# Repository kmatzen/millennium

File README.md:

# Millennium Project

The **Millennium Project** breathes new life into the Nortel Millennium public telephone by replacing much of its original electronics with modern hardware and software. The project integrates a Raspberry Pi Zero 2 W, two Arduinos, and a VoIP software stack while retaining all the original hardware, including the display, keypad, coin acceptor, magstripe reader, handset, and ringer speaker.

## Table of Contents

1. [Overview](#overview)
2. [Architecture](#architecture)
3. [Features](#features)
4. [Directory Structure](#directory-structure)
5. [Setup](#setup)
6. [Configuration](#configuration)
7. [Development](#development)
8. [Resources](#resources)
9. [License](#license)

---

## Overview

This project reimagines the functionality of the Nortel Millennium telephone by combining modern hardware and software while preserving its iconic hardware features:
- **Raspberry Pi Zero 2 W**: Manages the system, runs the VoIP stack, and interfaces with the original hardware.
- **Arduinos**: Control the keypad, display, and other peripherals.
- **Custom PCB**: Consolidates the connections between components.
- **Host Software**: Includes a daemon, plugin system, web dashboard, and ALSA audio configuration.
- **Preserved Hardware**: The original display, keypad, coin acceptor, magstripe reader, handset, and ringer speaker are retained and functional.

---

## Architecture

```
┌────────────────────────── Raspberry Pi Zero 2 W ───────────────────────────┐
│                                                                            │
│  ┌──────────────┐     ┌──────────────┐      ┌──────────────────────────┐   │
│  │ Daemon       │────▶│ PJSIP (VoIP) │      │ Web Dashboard :8081      │   │
│  │              │     └──────────────┘      │                          │   │
│  │ Plugins:     │                           │ - phone state            │   │
│  │ - Phone      │     ┌──────────────┐      │ - plugin switching       │   │
│  │ - Fortune    │     │ ALSA Audio   │      │ - OTA updates            │   │
│  │ - Jukebox    │     └──────────────┘      │ - health / metrics       │   │
│  │ - +4 games   │                           └──────────────────────────┘   │
│  └──────┬───────┘                                                          │
│         │ USB serial (9600 baud)                                           │
└─────────┬──────────────────────────────────────────────────────────────────┘
          │
┌─────────┴───────────────── Custom PCB (phonev6) ───────────────────────────┐
│                                                                            │
│  ┌──────────────────────┐ I2C      ┌────────────────────────┐              │
│  │ Display Arduino      │◀─────────│ Keypad Arduino         │              │
│  │ (millennium_beta)    │          │ (millennium_alpha)     │              │
│  │                      │          │                        │              │
│  │ - VFD display        │          │ - 4x7 keypad           │              │
│  │   (parallel 8-bit)   │          │ - magstripe reader     │              │
│  │ - coin validator     │          │ - hook switch          │              │
│  │   (SoftSerial)       │          └────────────────────────┘              │
│  └──────────────────────┘                                                  │
└────────────────────────────────────────────────────────────────────────────┘
```

**Data flow**: Keypad/hook/card events originate on the Keypad Arduino, are sent via I2C to the Display Arduino, which forwards them to the Raspberry Pi over USB serial. The daemon processes events through an event processor, dispatches them to the active plugin, and sends display updates back down the same path. VoIP calls are handled by PJSIP (PJSUA C API) with audio routed through ALSA (dmix + route plugins for mono channel splitting).

---

## Features

- **Pay phone operation**: Insert coins, dial numbers, make VoIP calls — authentic payphone experience
- **Plugin system**: Swap modes live — Classic Phone, Fortune Teller, Jukebox, plus games (Number Guess, Simon, Dial-A-Joke, Trivia). Write your own against the [plugin SDK](host/PLUGIN_AUTHORING.md); new plugins appear in the dashboard automatically
- **Emergency calls**: Dial 911, 311, or 0 without coins (configurable free numbers)
- **Dedicated credential-card support**: Swipe a random-token card for free calling or administration; payment cards are prohibited
- **Web dashboard**: Real-time phone state, plugin switching, health monitoring via WebSocket
- **Signed OTA updates**: Check, install, attest, and roll back immutable host and firmware releases. The unattended production design is documented in [host/docs/UNATTENDED_APPLIANCE.md](host/docs/UNATTENDED_APPLIANCE.md).
- **Audio tones**: DTMF, dial tone, busy tone, coin tone, ringback via ALSA
- **Idle timeout**: Automatically resets phone state after configurable inactivity period
- **State persistence**: Saves and restores coin balance and plugin state across restarts
- **Health monitoring**: Tracks serial connection, SIP registration, and daemon activity
- **Metrics collection**: Counters for calls, coins, keypresses, card swipes
- **Version tracking**: Build version and git hash displayed on dashboard
- **Scenario testing**: Simulator-based integration tests with simulated time
- **Full ARM appliance VM**: A Debian/QEMU lab runs the real daemon under
  systemd against a protocol-faithful virtual phone controller. See
  [tools/qemu/README.md](tools/qemu/README.md).

---

## Directory Structure

- **`Arduino/`**: Arduino sketches for the keypad and display microcontrollers, plus a Makefile for building and flashing.
- **`case/`**: 3D model files (`.blend` and `.stl`) for a custom enclosure. See [case/README.md](case/README.md) for dimensions and print settings.
- **`pcb/`**: KiCad schematic, PCB layout, BOM, and Gerber files for the custom PCB (phonev6).
- **`HARDWARE.md`**: Physical assembly reference — USB topology, cable routing, power budget, and component list.
- **`host/docs/UNATTENDED_APPLIANCE.md`**: Production design for signed full-device OTA and outbound remote maintenance.
- **`host/`**: Raspberry Pi software:
  - `daemon.c` — Main daemon loop and event routing
  - `plugins/` — Plugin implementations (classic_phone, fortune_teller, jukebox, number_guess, simon, dial_a_joke, trivia)
  - `plugin_sdk.c` — Plugin authoring facade (see [PLUGIN_AUTHORING.md](host/PLUGIN_AUTHORING.md))
  - `web_server.c` — HTTP server with dashboard and REST API
  - `audio_tones.c` — Tone generation (DTMF, dial tone, etc.)
  - `updater.c` — OTA update checker and applier
  - `simulator.c` — Test runner with scenario file support and simulated time
  - `tests/` — Unit tests and scenario test files
  - `systemd/` — Service file for the daemon
  - `daemon.conf.example` — Example configuration file
  - `asoundrc.example` — ALSA audio configuration for mono channel splitting
- **`tools/qemu/`**: Reproducible ARM VM, cloud-init provisioning, virtual MCU,
  lifecycle commands, and end-to-end smoke test.

---

## Setup

### 1. Arduino Firmware
Navigate to the `Arduino/` directory and follow the instructions in its [README](Arduino/README.md) to build and flash firmware to the microcontrollers.

### 2. PCB
The PCB files are in the `pcb/` directory. Upload the Gerber files to a PCB fabricator like JLCPCB for manufacturing. See the [pcb README](pcb/README.md) for details.

### 3. Host Software
Follow the [setup guide](host/SETUP.md) for full step-by-step instructions, or use the quick install:

```bash
cd host
make daemon        # Build the daemon
sudo make install  # Install to /usr/local/bin and set up systemd
```

See the [host README](host/README.md) for dependency installation (PJSIP, ALSA) and audio configuration.

### 4. Configuration
Copy and edit the configuration file:

```bash
sudo cp host/daemon.conf.example /etc/millennium/daemon.conf
sudo nano /etc/millennium/daemon.conf
```

See [Configuration](#configuration) below for all available options.

---

## Configuration

The daemon reads configuration from `/etc/millennium/daemon.conf`. See `host/daemon.conf.example` for a complete annotated example. Key settings:

| Key | Default | Description |
|-----|---------|-------------|
| `hardware.display_device` | `/dev/serial/by-id/usb-Arduino_LLC_Millennium_Beta-if00` | Serial device for display Arduino |
| `hardware.baud_rate` | `9600` | Serial baud rate |
| `call.cost_cents` | `50` | Cost per call in cents |
| `call.timeout_seconds` | `300` | Maximum call duration |
| `call.free_numbers` | `911,311,0` | Comma-separated numbers that bypass coin requirement |
| `call.idle_timeout_seconds` | `60` | Seconds of inactivity before phone resets |
| `card.enabled` | `true` | Enable magstripe card support |
| `card.free_tokens` | *(empty)* | Random 16-digit dedicated-card tokens for free calling |
| `card.admin_tokens` | *(empty)* | Random 16-digit dedicated-card tokens for administration |
| `web_server.enabled` | `true` | Enable the web dashboard |
| `web_server.port` | `80` | Web dashboard port |
| `system.source_dir` | `/home/millennium/millennium` | Development-only source directory |

---

## Development

### Building and testing

```bash
cd host
make test          # Build simulator + unit tests, run both
make daemon        # Build the full daemon (requires PJSIP/libpjproject on the Pi)
make clean         # Remove all build artifacts
```

### Running tests locally

Tests run on any platform (macOS, Linux) without PJSIP or ALSA — the simulator stubs out hardware dependencies:

```bash
cd host
make test
```

This runs:
- **Unit tests**: Config, daemon state, plugins, emergency numbers, card config, updater
- **Scenario tests**: Full integration tests (basic call, timeout, emergency, card swipe, hook lifecycle, state persistence, display scrolling, idle timeout)

### Adding a plugin

See [host/PLUGIN_AUTHORING.md](host/PLUGIN_AUTHORING.md) for the full guide. In short:

1. Create `host/plugins/your_plugin.c` (write it against [plugin_sdk.h](host/plugin_sdk.h))
2. Implement handler functions for the events you care about (coin, keypad, hook, call state, card, tick)
3. Register with `plugins_register()` in a `register_your_plugin()` function
4. Call the registration function from `plugins_init()` in `plugins.c`
5. Add the `.o` file to the Makefile build targets (daemon, `SIM_OBJS`, `UNIT_TEST_OBJS`)
6. Run `make test` — your plugin then appears in the dashboard automatically

### Coding style

- C89 across the whole codebase, compiled with `-std=gnu89` (the C89 language plus the GNU extensions the ALSA/PJSIP headers require, e.g. `inline`; strict `-std=c89` can't parse those headers)
- `-Wall -Wextra -Wdeclaration-after-statement -Werror` on every target — warnings are errors, and `-Wdeclaration-after-statement` keeps the source free of C99-style mixed declarations
- No unnecessary comments — code should be self-documenting

---

## Resources

This project draws on several resources for understanding and interfacing with the Nortel Millennium telephone's hardware:

1. **General Millennium Payphone Documentation**
   The [Millennium Payphone Wiki](https://wiki.muc.ccc.de/millennium:start) provides extensive documentation on the phone's hardware and protocols.
   - **Coin Validator Protocol**: Used the documented higher-level protocol to interface with the coin validator.
   - **EEPROM Data**: Referenced for configuring the coin validator to accept Canadian currency.

2. **Display Documentation**
   A detailed discussion on the Noritake CU20026SCPB-T23A VFD display can be found in this [HardForum thread](https://hardforum.com/threads/noritake-cu20026scpb-t23a-20-x-2-vfd-modulel.1132806/). This was essential for understanding and controlling the display.

3. **Device Pinouts**
   The [New Fire Millennium Payphone Page](http://www.newfire.org/payphones/millennium/) includes pinout diagrams for various components, which were critical when developing the Arduino sketches.

4. **Millennium Phone Source**
   The Millennium phone used in this project was sourced from [Ballard Reuse](https://ballardreuse.com/) in Seattle, a store specializing in salvaged and reusable materials.

---

## License

This project is licensed under the MIT License. See [LICENSE](LICENSE) for details.

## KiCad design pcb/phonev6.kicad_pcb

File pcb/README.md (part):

# PCB Design

This directory contains the PCB design files created with [KiCad](https://www.kicad.org/).

## Design History

- **phonev2** (removed): Dual LM358 op-amps, raw power connector, pin headers for audio.
- **phonev4** (earlier fabrication): Single LM386 power amplifier for ringer only,
  XL6009 boost converter, RJ9 and 3.5mm jacks. Had two design flaws: speaker
  output coupling (#42) and unamplified handset earpiece (#44).
- **phonev5** (previous schematic): TDA2822M dual-channel amplifier replacing the
  LM386, fixing both audio design flaws. Adds reverse polarity protection, ESD
  protection, power LED, fuse, test points, and improved I2C pull-ups.
- **phonev6 (current — fabricated and installed)**: through-hole → SMD migration of
  the phonev5 design, plus a `make verify` guardrail suite (netlist sync, footprint
  parity, pinout and footprint checks, ERC, DRC) that must be all-green before
  ordering. This is the revision currently installed in the phone.

## Audio Circuit (TDA2822M)

The TDA2822M is a dual low-voltage audio power amplifier in a DIP-8 package
(same footprint as the LM386 it replaces). It provides two independent amplified
channels, solving both the speaker coupling and quiet handset issues.

### Signal Paths

```
USB audio card (stereo 3.5mm)
  ├─ Left channel → J7 tip → C_inA → TDA2822 IN_A (pin 3)
  │                                    → OUT_A (pin 1) → C_outA → speaker_front+ → ringer
  │
  └─ Right channel → J7 ring → C_inB → TDA2822 IN_B (pin 4)
                                        → OUT_B (pin 5) → C_outB → speaker_receiver+ → J4 RJ9 → handset
```

Each channel has its own input coupling capacitor (100nF) and output coupling
capacitor (100µF). The channels are electrically isolated inside the TDA2822M,
eliminating the crosstalk present in the v4 LM386 design.

### TDA2822M Pin Connections

| Pin | Function | Net                               |
|-----|----------|-----------------------------------|
| 1   | OUT_A    | → C_outA → `speaker_front+`       |
| 2   | GND      | `gnd`                             |
| 3   | IN_A     | `speaker_front_pre+` via C_inA    |
| 4   | IN_B     | `speaker_receiver_pre+` via C_inB |
| 5   | OUT_B    | → C_outB → `speaker_receiver+`    |
| 6   | V+       | `5V_MAIN`                         |
| 7   | RIPPLE   | → C_ripple (4.7µF) to GND         |
| 8   | NC       | Not connected                     |

### Component Values

| Ref       | Value     | Purpose                              |
|-----------|-----------|--------------------------------------|
| C_inA     | 100nF     | Input coupling, channel A (ringer)   |
| C_inB     | 100nF     | Input coupling, channel B (handset)  |
| C_outA    | 100µF 16V | Output coupling, channel A (ringer)  |
| C_outB    | 100µF 16V | Output coupling, channel B (handset) |
| C_vcc     | 100µF 16V | Vcc bypass                           |
| C_ripple  | 4.7µF     | Ripple rejection (pin 7)             |
| C_dec     | 100nF     | Vcc decoupling                       |

## Bill of Materials

| Ref      | Value / Part                | Qty | Footprint                         | Notes                                                    |
|----------|-----------------------------|-----|-----------------------------------|----------------------------------------------------------|
| A1       | Arduino Micro (keypad)      | 1   | Socket headers                    | Millennium Alpha board                                   |
| A2       | Arduino Micro (display)     | 1   | Socket headers                    | Millennium Beta board                                    |
| A3       | Raspberry Pi Zero WH        | 1   | ADA3708 footprint                 | Adafruit ADA3708                                         |
| U1       | XL6009 boost converter      | 1   | Module                            | 12V output (from 5V input), coin validator supply        |
| U2       | TDA2822M                    | 1   | DIP-8                             | Dual audio amplifier                                     |
| R1       | 4.7kΩ resistor              | 1   | Axial                             | I2C pull-up (SDA)                                        |
| R2       | 4.7kΩ resistor              | 1   | Axial                             | I2C pull-up (SCL)                                        |
| R3       | 1kΩ resistor                | 1   | Axial                             | Power LED current limit                                  |
| C_inA    | 100nF ceramic               | 1   | Axial L3.8mm THT                  | TDA2822 ch A input coupling                              |
| C_inB    | 100nF ceramic               | 1   | Axial L3.8mm THT                  | TDA2822 ch B input coupling                              |
| C_outA   | 100µF 16V electrolytic      | 1   | Radial D8mm P3.8mm                | TDA2822 ch A output coupling                             |
| C_outB   | 100µF 16V electrolytic      | 1   | Radial D8mm P3.8mm                | TDA2822 ch B output coupling                             |
| C_vcc    | 100µF 16V electrolytic      | 1   | Radial D8mm P3.8mm                | TDA2822 Vcc bypass                                       |
| C_ripple | 4.7µF electrolytic          | 1   | Radial D5mm P2.0mm                | TDA2822 ripple rejection                                 |
| C_dec    | 100nF ceramic               | 1   | Axial L3.8mm THT                  | TDA2822 Vcc decoupling                                   |
| C-*      | 100nF ceramic               | 5   | Axial L3.8mm THT                  | Decoupling (see below)                                   |
| D1–D3    | P6KE6.8CA                   | 3   | DO-15 (THT axial)                 | TVS clamp signal lines to GND (600W bidirectional)       |
| Q1       | AO3401A P-ch MOSFET         | 1   | SOT-23 (SMD, JLCPCB basic C15127) | Reverse polarity protection                              |
| F1       | 1A PTC fuse                 | 1   | Radial D10mm THT                  | Resettable overcurrent fuse                              |
| D4       | Red LED (0603, C2286 basic) | 1   | LED_0603 SMD                      | Power indicator                                          |
| J1       | Coin validator              | 1   | 2x5 pin header                    | 10-pin IDC                                               |
| J2       | Keypad                      | 1   | 2x10 pin header                   | 20-pin IDC                                               |
| J3       | VFD display                 | 1   | 2x13 pin header                   | 26-pin IDC                                               |
| J4       | Handset (RJ9)               | 1   | RJ9 jack                          | 4P4C handset connector                                   |
| J5       | Microphone                  | 1   | 3.5mm stereo jack                 | Handset mic input                                        |
| J6       | Card reader                 | 1   | 2x7 pin header                    | 14-pin for magstripe reader                              |
| J7       | Speaker                     | 1   | 3.5mm stereo jack                 | Stereo audio from USB card                               |
| TP1–5    | Test points                 | 5   | Through-hole loop D2.5mm          | 5V_MAIN, Pi 3.3V, GND, SDA, SCL (see Test Points section)|

### Decoupling Capacitors (C-*)

| Ref                | Location                |
|--------------------|-------------------------|
| C-arduino1         | Near keypad Arduino     |
| C-arduino-display1 | Near display Arduino    |
| C-raspi1           | Near Raspberry Pi       |
| C-coin1            | Near coin connector     |
| C-card1            | Near card reader        |

## Protection Circuits

### Reverse Polarity Protection (Q1)

A P-channel MOSFET (AO3401A, SOT-23 SMD; JLCPCB basic C15127) on the incoming 5V rail protects
against accidental reverse-polarity connections. Q1 is placed on the power
input *before* distribution and *before* feeding U1 IN+. The MOSFET's body
diode conducts during normal operation with near-zero voltage drop, and blocks
current when polarity is reversed.

### ESD / TVS Protection (D1, D2, D3)

Three P6KE6.8CA TVS diodes (600W bidirectional, THT DO-15) protect signal
lines from ESD and transients. Each clamps between the protected signal and
GND—one pin to signal, one to GND. D1 protects J4 (handset); D2 protects
speaker_front+ (ringer output from TDA2822); D3 protects the third signal
line. These protect against back-EMF and ESD on external connectors.

### Overcurrent Protection (F1)

A 1A resettable PTC fuse (F1) is placed on the incoming 5V rail, in series
with Q1, before power distribution and before U1. It protects the entire board
(including the boost converter input) from downstream shorts. The fuse
self-resets when the fault is cleared.

### Power Indicator (D4, R3)

A red LED on the 5V_MAIN rail provides visual confirmation that the board is
powered, useful when debugging inside the payphone enclosure.

## Connector Pinouts

### J1 — Coin Validator (2x5)

The coin validator is powered from the 12V_COIN rail (U1 output). The PCB
routes SoftwareSerial (600 baud) from the display Arduino pins 14 (RX) and 23
(TX), plus a reset line from pin 15. See the coin validator documentation for
the serial protocol.

### J2 — Keypad (2x10)

Routes to the keypad Arduino's row pins (6–9) and column pins (10–13, 18–20),
plus the hook switch pins (4, 5, 21). See `Arduino/PINOUT.md` for the complete
mapping.

### J3 — VFD Display (2x13)

8-bit parallel data bus (D0–D7) plus control signals (WR, AD, RD, CS, TEST,
RESET) routed from the display Arduino. See `Arduino/PINOUT.md` for the pin-
to-VFD-pin mapping with wire colors.

### J4 — Handset (RJ9)

| Pin | Signal              |
|-----|---------------------|
| 1   | `mic+`              |
| 2   | `speaker_receiver+` |
| 3   | `gnd`               |
| 4   | `gnd`               |

### J6 — Card Reader (2x7)

MagStripe reader connections routed to the keypad Arduino: CLS (pin 22),
RDT/data (pin 0), RCL/clock (pin 1).

### J7 — Speaker/Audio (3.5mm stereo)

| Contact | Signal                  | Destination              |
|---------|-------------------------|--------------------------|
| Tip     | `speaker_receiver_pre+` | → TDA2822 ch B → handset |
| Ring    | `speaker_front_pre+`    | → TDA2822 ch A → ringer  |
| Sleeve  | `gnd`                   | Ground                   |

## I2C Bus

The two Arduinos communicate over I2C (SDA/SCL). The PCB provides 4.7kΩ pull-up
resistors (R1, R2) to 5V on both lines — the standard recommended value for
100kHz I2C.

## Power Distribution

The board is powered from an external 5V supply. Power flows as follows:

1. **Incoming 5V** enters the board and passes through:
   - Q1 (reverse polarity protection)
   - F1 (PTC fuse)
2. **5V_MAIN rail** (after Q1 and F1) distributes to:
   - Both Arduino Micro boards (5V pin)
   - Raspberry Pi Zero WH (5V via GPIO header)
   - VFD display (5V logic supply; VFD filament uses its own internal supply)
   - TDA2822M amplifier (pin 6)
   - MagStripe reader (5V via Arduino)
   - U1 IN+ (boost converter input)

3. **12V_COIN rail**: U1 (XL6009) boosts 5V → 12V. XL6009 pins: IN+ = 5V_MAIN,
   IN- = GND, OUT- = GND, OUT+ = 12V_COIN. The 12V_COIN rail powers the coin
   validator only (J1). Nothing else on the board uses 12V.

## Test Points

| Label | Signal   | Purpose                             |
|-------|----------|-------------------------------------|
| TP1   | 5V_MAIN  | Main 5V power rail                   |
| TP2   | 3.3V     | Pi's 3.3V output (if accessible)    |
| TP3   | GND      | Ground reference                    |
| TP4   | SDA      | I2C data (Arduino ↔ Arduino)        |
| TP5   | SCL      | I2C clock                           |
| TP6   | 12V_COIN | Boosted 12V rail for coin validator |

**Note on USB connectivity**: Arduino ↔ Pi communication is via USB through an
external hub. There are no discrete USB serial TX/RX nets on the PCB; TP6 and
TP7 in older docs referred to USB serial, but that path does not exist as PCB
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
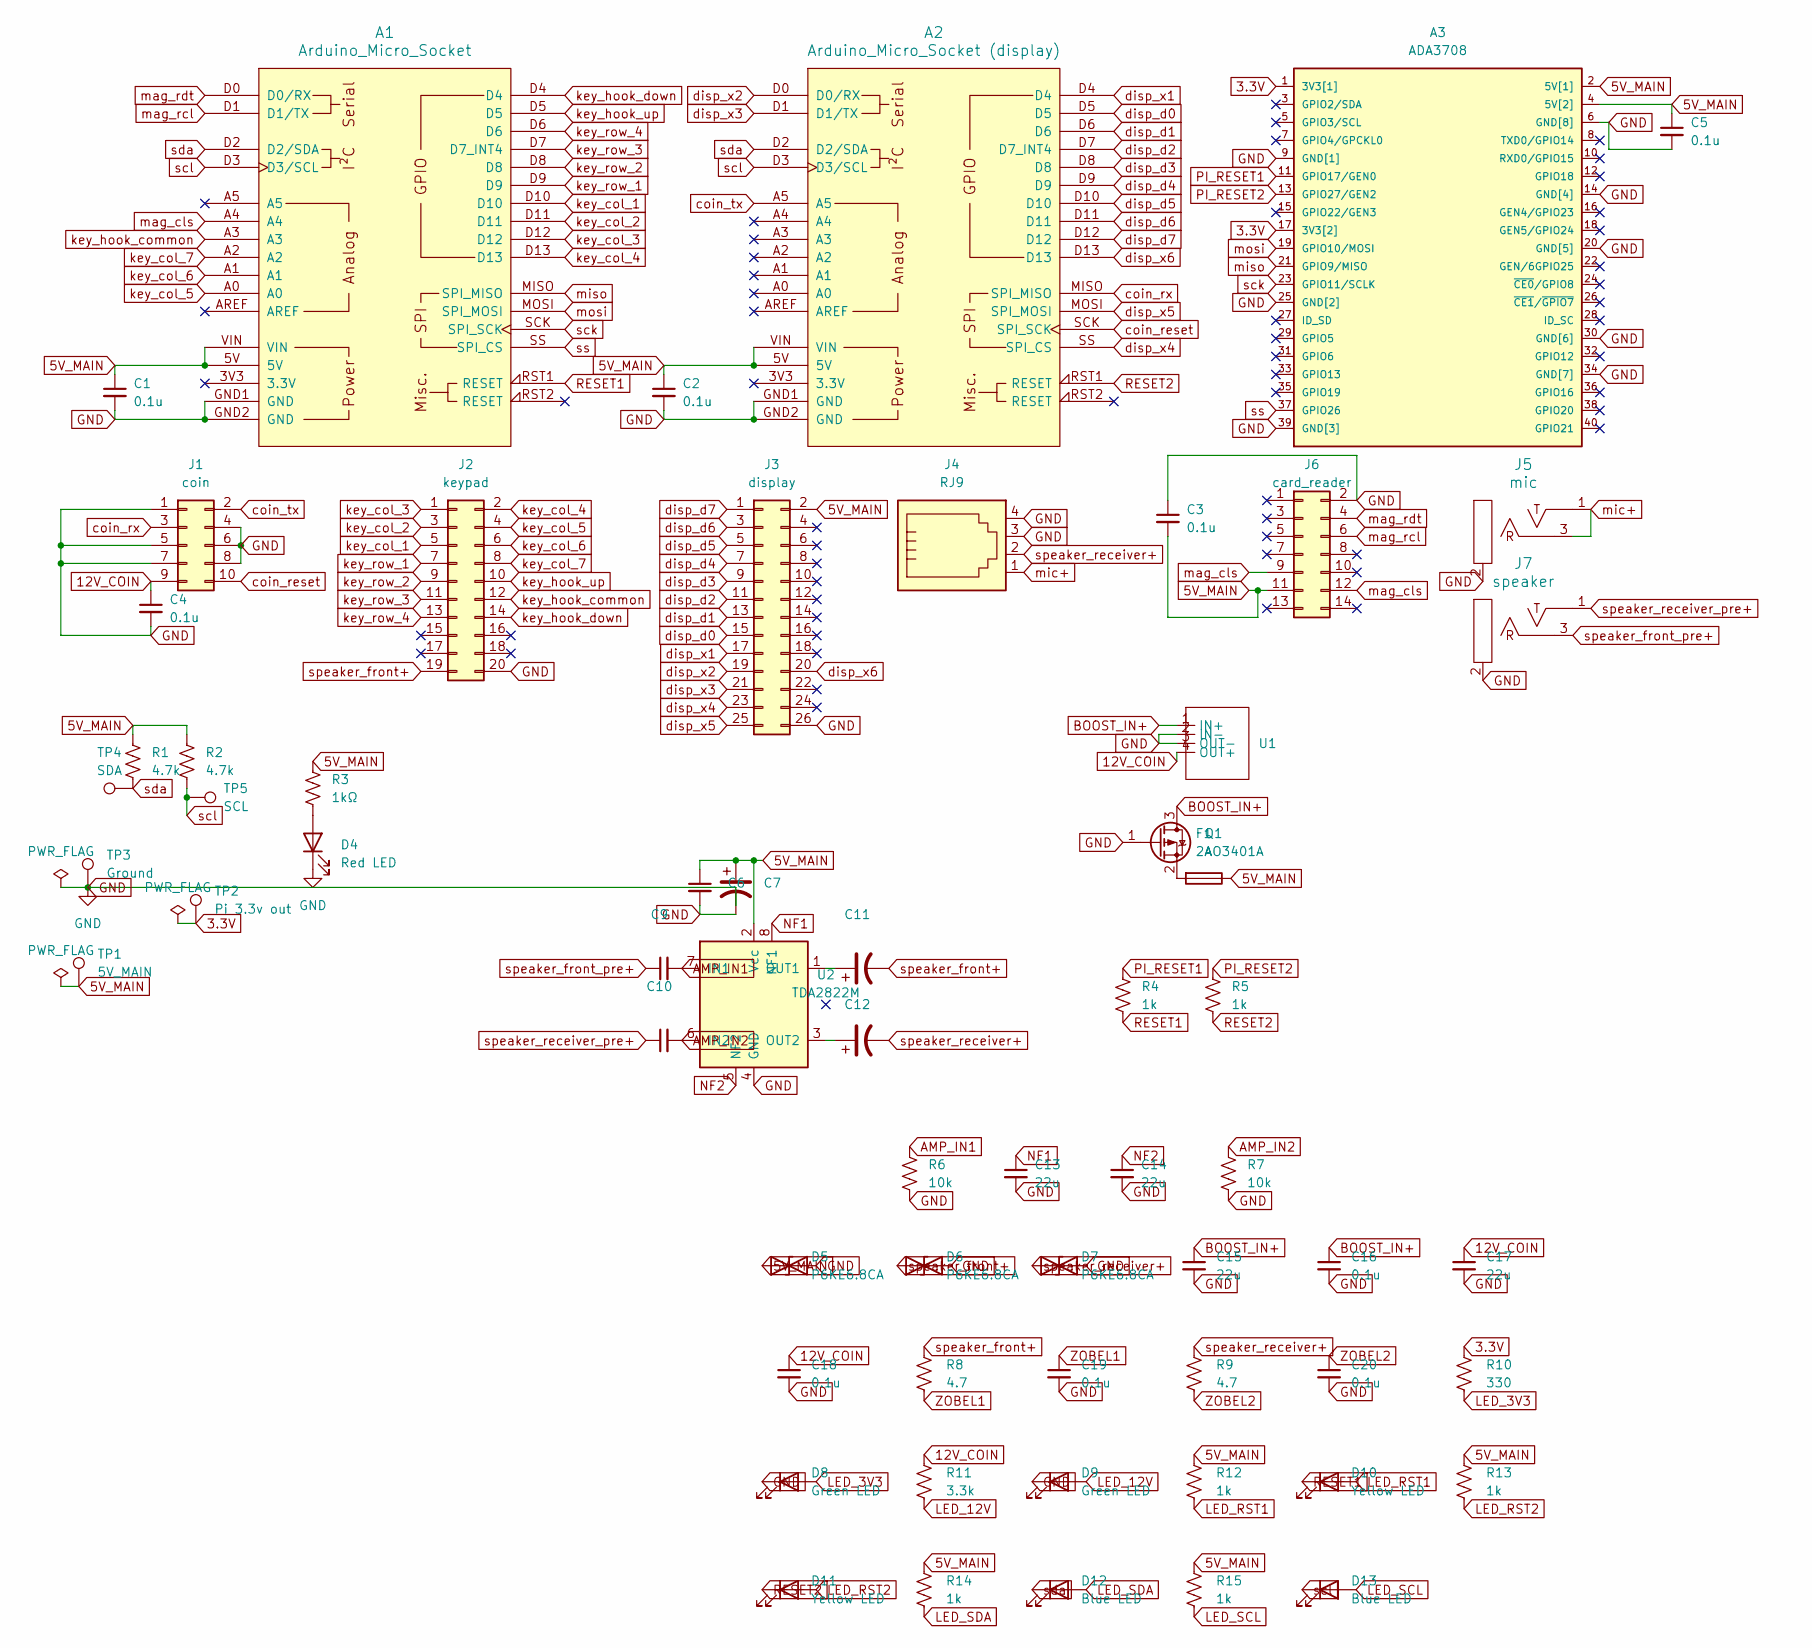
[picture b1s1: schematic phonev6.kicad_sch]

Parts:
A1: Arduino_Micro_Socket
A2: Arduino_Micro_Socket (display); Arduino_Micro_Socket
A3: ADA3708; ADA3708_RPI-ZERO
C1, C2, C3, C4, C5, C16, C18, C19, C20: 0.1u; C_0805_2012Metric; LCSC C49678
C6, C9, C10: 100nF; C_0805_2012Metric; LCSC C49678
C7, C11, C12: 100µF 16V; CP_Elec_6.3x5.4; LCSC C37308
C13, C14, C15, C17: 22u; C_0805_2012Metric; LCSC C45783
D4: Red LED; LED_0805_2012Metric; LCSC C2297
D5, D6, D7: P6KE6.8CA; D_SMB; LCSC C78395
D8, D9: Green LED; LED_0805_2012Metric; LCSC C2297
D10, D11: Yellow LED; LED_0805_2012Metric; LCSC C2296
D12, D13: Blue LED; LED_0805_2012Metric; LCSC C2293
F1: 2A; Fuse_1812_4532Metric; LCSC C2649901
J1: coin; IDC-Header_2x05_P2.54mm_Vertical
J2: keypad; IDC-Header_2x10_P2.54mm_Vertical
J3: display; IDC-Header_2x13_P2.54mm_Vertical
J4: RJ9; RJ9_Evercom_5301-440xxx_Horizontal
J5: mic; AUDIO-TH_HOOYA_PJ-320; Part Number WQP-WQP419GR
J6: card_reader; IDC-Header_2x07_P2.54mm_Vertical
J7: speaker; AUDIO-TH_HOOYA_PJ-320; Part Number WQP-WQP419GR; LCSC C2884926
Q1: AO3401A; SOT-23; LCSC C15127
R1, R2: 4.7k; R_0805_2012Metric; LCSC C17673
R3: 1kΩ; R_0805_2012Metric; LCSC C17513
R4, R5, R12, R13, R14, R15: 1k; R_0805_2012Metric; LCSC C17513
R6, R7: 10k; R_0805_2012Metric; LCSC C17414
R8, R9: 4.7; R_0805_2012Metric; LCSC C2889556
R10: 330; R_0805_2012Metric; LCSC C17630
R11: 3.3k; R_0805_2012Metric; LCSC C26010
TP1: 5V_MAIN; TestPoint_Loop_D2.50mm_Drill1.0mm
TP2: Pi 3.3v out; TestPoint_Loop_D2.50mm_Drill1.0mm
TP3: Ground; TestPoint_Loop_D2.50mm_Drill1.0mm
TP4: SDA; TestPoint_Loop_D2.50mm_Drill1.0mm
TP5: SCL; TestPoint_Loop_D2.50mm_Drill1.0mm
U1: XL6009_module
U2: TDA2822M; SOIC-8_3.9x4.9mm_P1.27mm; LCSC C725341

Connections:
3.3V: A3.1 (3V3[1]), A3.17 (3V3[2]), R10.1, TP2.1
5V_MAIN: A1.5V, A1.VIN, A2.5V, A2.VIN, A3.2 (5V[1]), A3.4 (5V[2]), C1.1, C2.1, C3.2, C5.1, C6.1, C7.1, D5.1, F1.1, J3.2, J6.11, R1.1, R2.1, R3.1, R12.1, R13.1, R14.1, R15.1, TP1.1, U2.2 (Vcc)
12V_COIN: C4.1, C17.1, C18.1, J1.9, R11.1, U1.4 (OUT+)
AMP_IN1: C9.2, R6.1, U2.7 (IN1)
AMP_IN2: C10.2, R7.1, U2.6 (IN2)
BOOST_IN+: C15.1, C16.1, Q1.3 (D), U1.1 (IN+)
GND: A1.GND1 (GND), A1.GND2 (GND), A2.GND1 (GND), A2.GND2 (GND), A3.6 (GND[8]), A3.9 (GND[1]), A3.14 (GND[4]), A3.20 (GND[5]), A3.25 (GND[2]), A3.30 (GND[6]), A3.34 (GND[7]), A3.39 (GND[3]), C1.2, C2.2, C3.1, C4.2, C5.2, C6.2, C7.2, C13.2, C14.2, C15.2, C16.2, C17.2, C18.2, C19.2, C20.2, D4.1 (K), D5.2, D6.2, D7.2, D8.1 (K), D9.1 (K), J1.1, J1.4, J1.5, J1.6, J1.7, J1.8, J2.20, J3.26, J4.3, J4.4, J5.2 (SHEILD), J6.2, J7.2 (SHEILD), Q1.1 (G), R6.2, R7.2, TP3.1, U1.2 (IN-), U1.3 (OUT-), U2.4 (GND); also elsewhere on the board
LED_3V3: D8.2 (A), R10.2
LED_12V: D9.2 (A), R11.2
LED_RST1: D10.2 (A), R12.2
LED_RST2: D11.2 (A), R13.2
LED_SCL: D13.2 (A), R15.2
LED_SDA: D12.2 (A), R14.2
NF1: C13.1, U2.8 (NF1)
NF2: C14.1, U2.5 (NF2)
unnamed: D4.2 (A), R3.2
unnamed: F1.2, Q1.2 (S)
unnamed: C11.1, U2.1 (OUT1)
unnamed: C12.1, U2.3 (OUT2)
PI_RESET1: A3.11 (GPIO17/GEN0), R4.1
PI_RESET2: A3.13 (GPIO27/GEN2), R5.1
RESET1: A1.RST1 (RESET), D10.1 (K), R4.2
RESET2: A2.RST1 (RESET), D11.1 (K), R5.2
ZOBEL1: C19.1, R8.2
ZOBEL2: C20.1, R9.2
coin_reset: A2.SCK (SPI_SCK), J1.10
coin_rx: A2.MISO (SPI_MISO), J1.3
coin_tx: A2.A5, J1.2
disp_d0: A2.D5, J3.15
disp_d1: A2.D6, J3.13
disp_d2: A2.D7 (D7_INT4), J3.11
disp_d3: A2.D8, J3.9
disp_d4: A2.D9, J3.7
disp_d5: A2.D10, J3.5
disp_d6: A2.D11, J3.3
disp_d7: A2.D12, J3.1
disp_x1: A2.D4, J3.17
disp_x2: A2.D0 (D0/RX), J3.19
disp_x3: A2.D1 (D1/TX), J3.21
disp_x4: A2.SS (SPI_CS), J3.23
disp_x5: A2.MOSI (SPI_MOSI), J3.25
disp_x6: A2.D13, J3.20
key_col_1: A1.D10, J2.5
key_col_2: A1.D11, J2.3
key_col_3: A1.D12, J2.1
key_col_4: A1.D13, J2.2
key_col_5: A1.A0, J2.4
key_col_6: A1.A1, J2.6
key_col_7: A1.A2, J2.8
key_hook_common: A1.A3, J2.12
key_hook_down: A1.D4, J2.14
key_hook_up: A1.D5, J2.10
key_row_1: A1.D9, J2.7
key_row_2: A1.D8, J2.9
key_row_3: A1.D7 (D7_INT4), J2.11
key_row_4: A1.D6, J2.13
mag_cls: A1.A4, J6.9, J6.12
mag_rcl: A1.D1 (D1/TX), J6.6
mag_rdt: A1.D0 (D0/RX), J6.4
mic+: J4.1, J5.1 (SIG), J5.3 (SW)
miso: A1.MISO (SPI_MISO), A3.21 (GPIO9/MISO)
mosi: A1.MOSI (SPI_MOSI), A3.19 (GPIO10/MOSI)
sck: A1.SCK (SPI_SCK), A3.23 (GPIO11/SCLK)
scl: A1.D3 (D3/SCL), A2.D3 (D3/SCL), D13.1 (K), R2.2, TP5.1
sda: A1.D2 (D2/SDA), A2.D2 (D2/SDA), D12.1 (K), R1.2, TP4.1
speaker_front+: C11.2, D6.1, J2.19, R8.1
speaker_front_pre+: C9.1, J7.3 (SW)
speaker_receiver+: C12.2, D7.1, J4.2, R9.1
speaker_receiver_pre+: C10.1, J7.1 (SIG)
ss: A1.SS (SPI_CS), A3.37 (GPIO26)

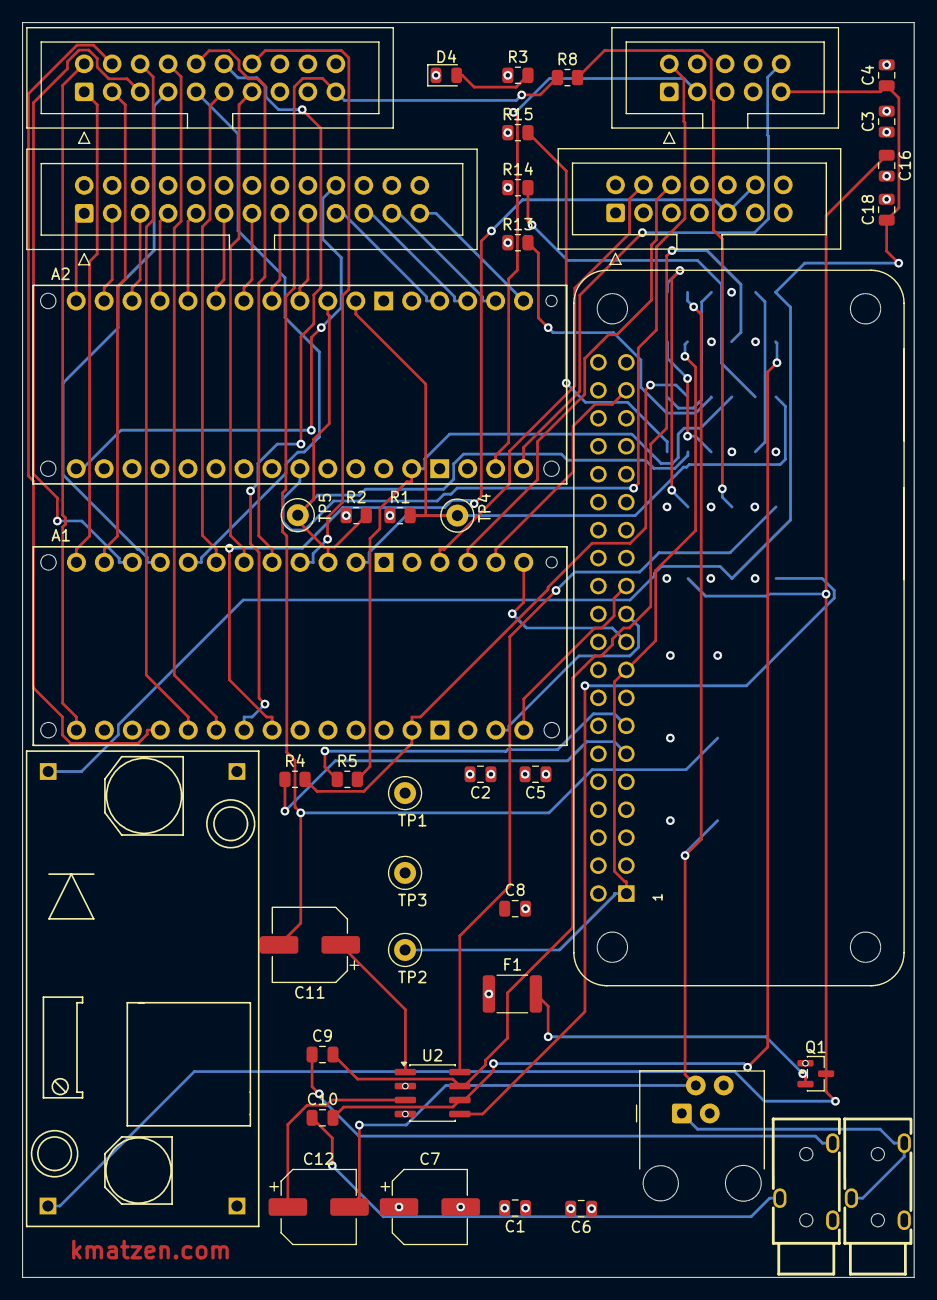
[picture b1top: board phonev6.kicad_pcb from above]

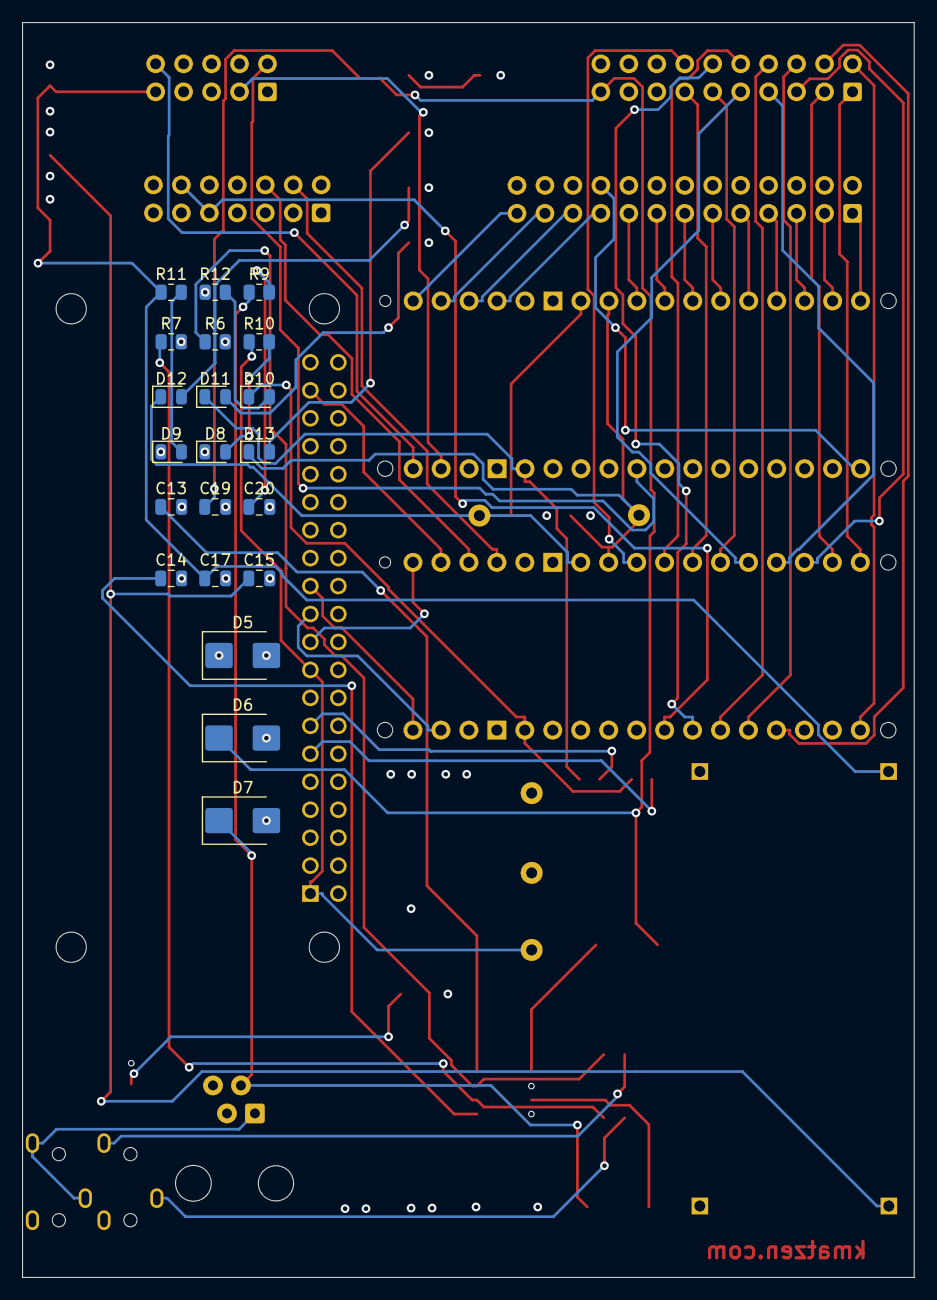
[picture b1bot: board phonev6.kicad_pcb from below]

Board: 4 copper layers, 81.0 x 114.0 mm, 64 parts (21 on the bottom side), 70 nets.

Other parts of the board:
C8: 4.7µF; C_0805_2012Metric

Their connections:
GND: C8.2; also elsewhere on the board

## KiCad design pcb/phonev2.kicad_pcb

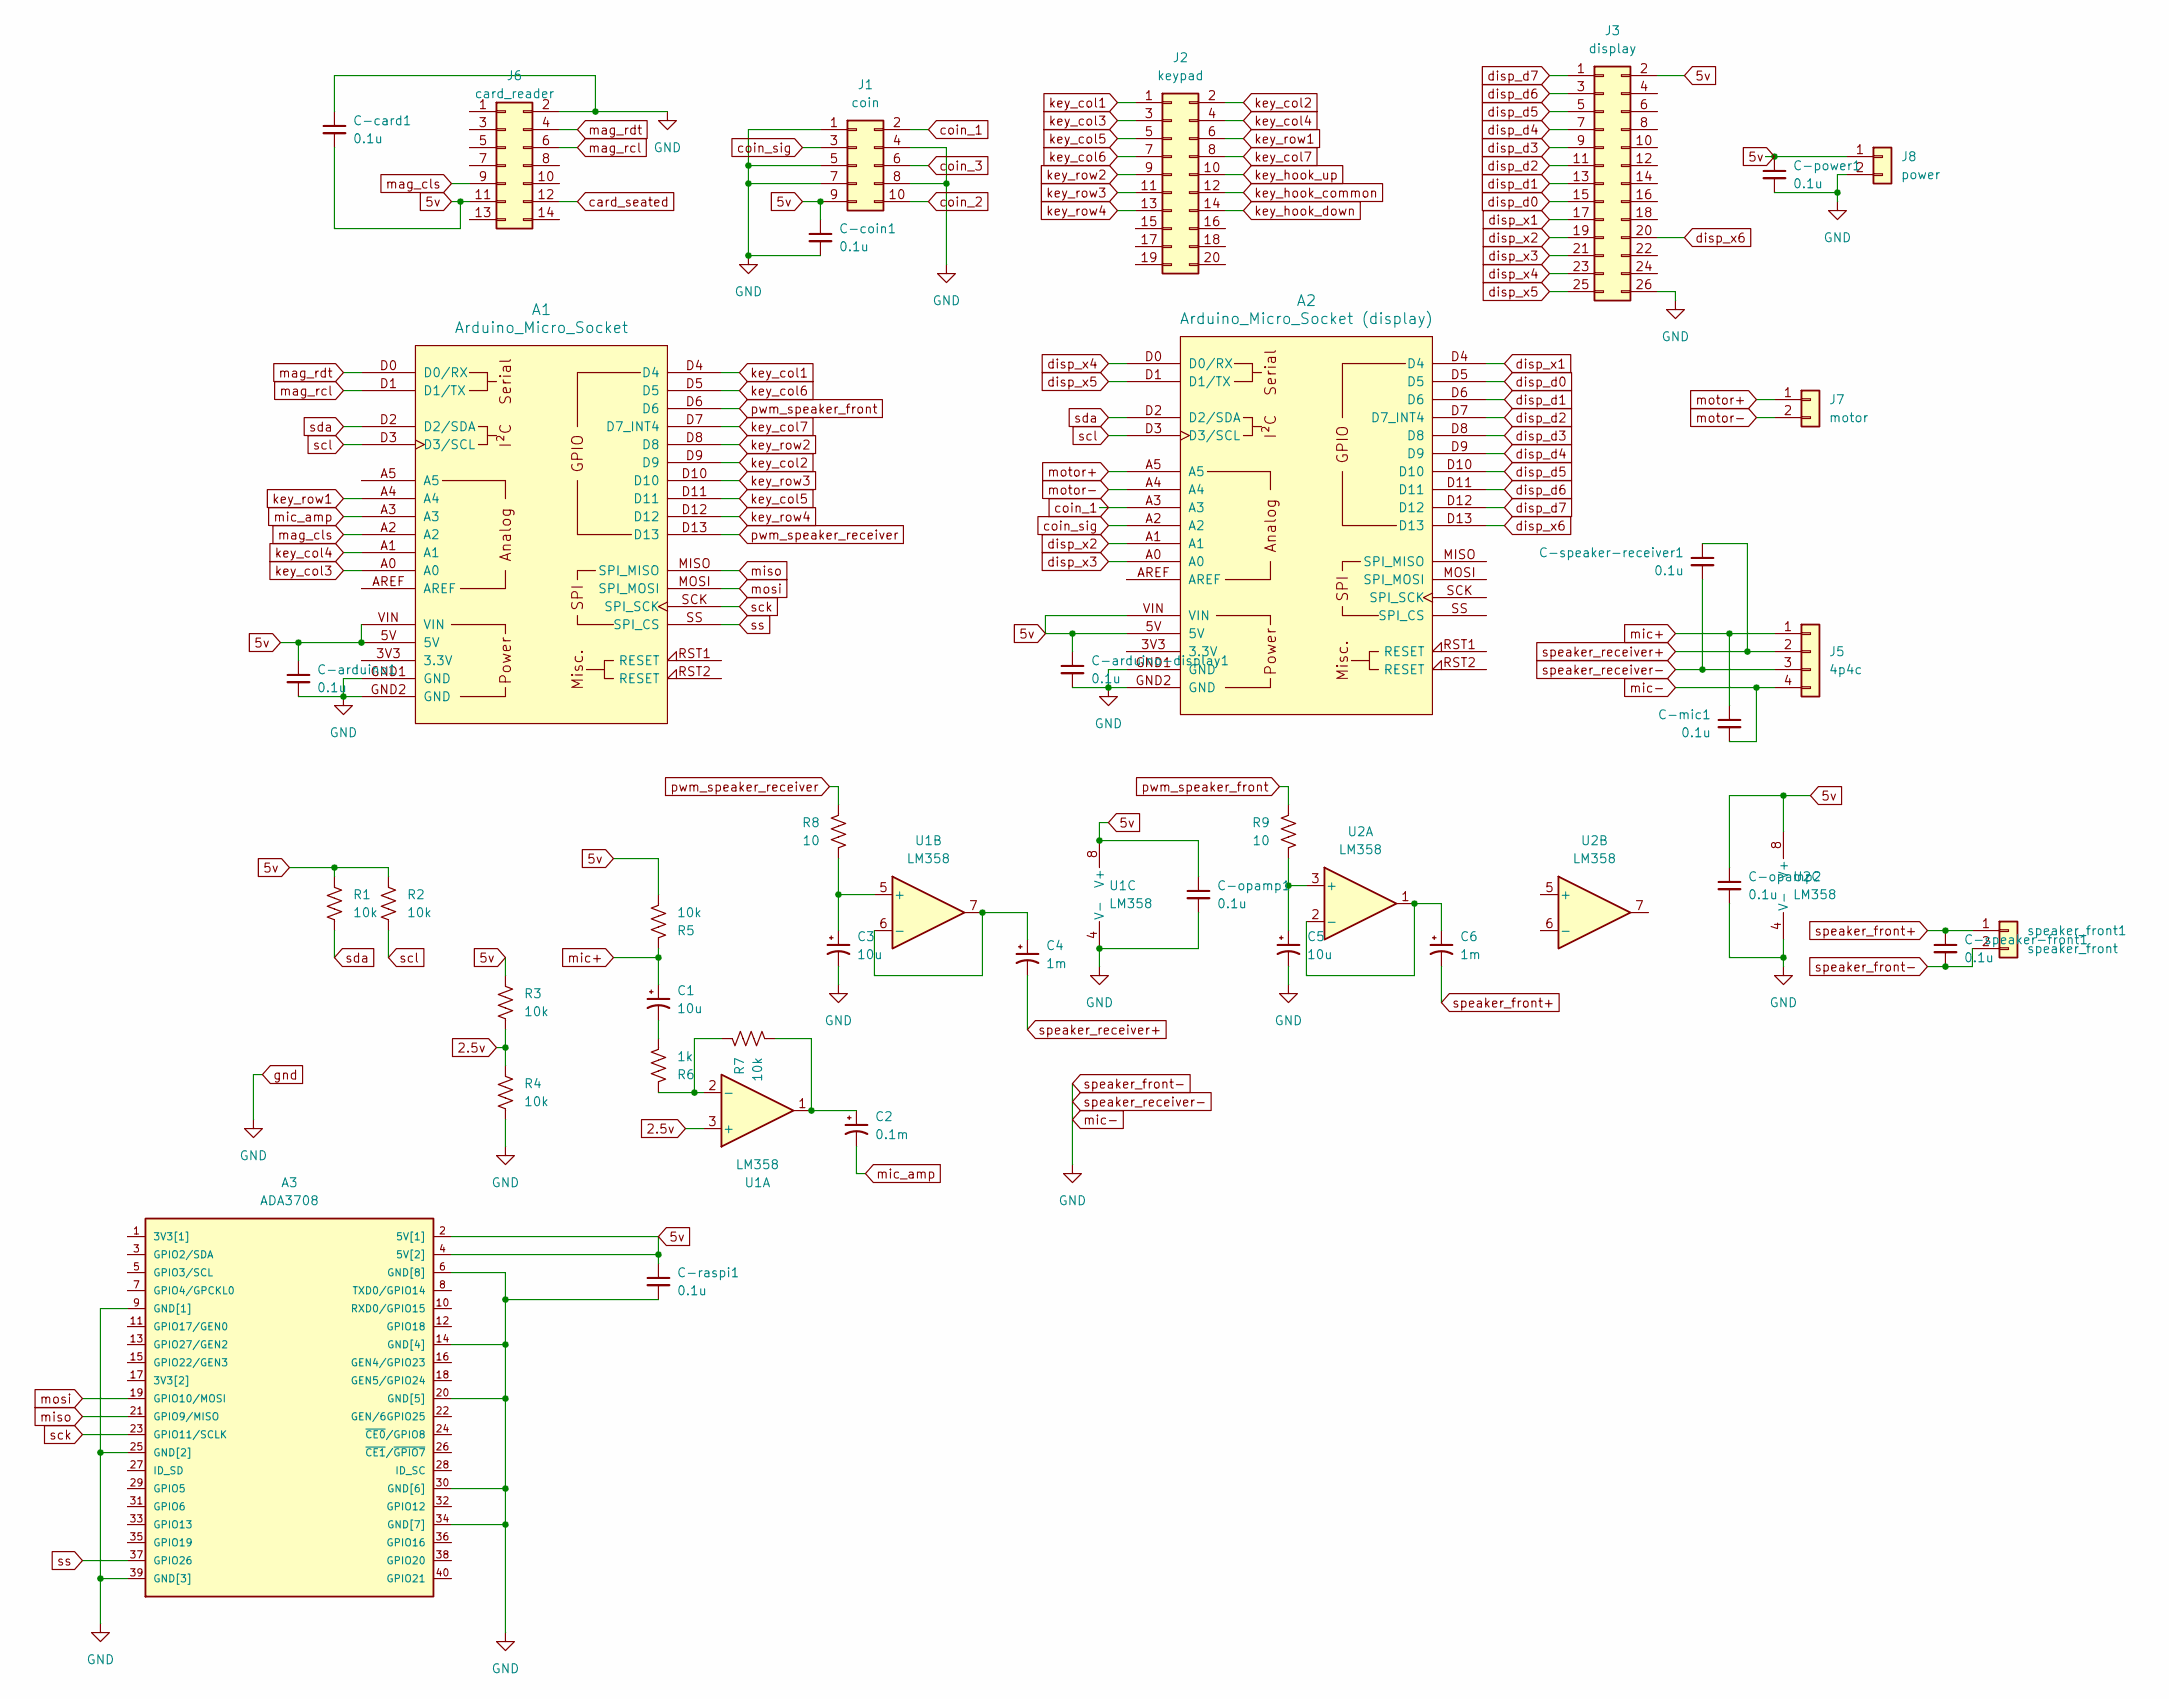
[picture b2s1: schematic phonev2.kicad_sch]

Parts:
A1: Arduino_Micro_Socket
A2: Arduino_Micro_Socket (display); Arduino_Micro_Socket
A3: ADA3708; ADA3708_RPI-ZERO
C1, C3, C5: 10u; C_Radial_D6.3mm_H5.0mm_P2.50mm
C2: 0.1m; C_Radial_D6.3mm_H5.0mm_P2.50mm
C4, C6: 1m; C_Radial_D6.3mm_H5.0mm_P2.50mm
C-arduino1: 0.1u; C_Axial_L3.8mm_D2.6mm_P7.50mm_Horizontal
C-arduino-display1: 0.1u; C_Axial_L3.8mm_D2.6mm_P7.50mm_Horizontal
C-card1: 0.1u; C_Axial_L3.8mm_D2.6mm_P7.50mm_Horizontal
C-coin1: 0.1u; C_Axial_L3.8mm_D2.6mm_P7.50mm_Horizontal
C-mic1: 0.1u; C_Axial_L3.8mm_D2.6mm_P7.50mm_Horizontal
C-opamp1, C-opamp2: 0.1u; C_Axial_L3.8mm_D2.6mm_P7.50mm_Horizontal
C-power1: 0.1u; C_Axial_L3.8mm_D2.6mm_P7.50mm_Horizontal
C-raspi1: 0.1u; C_Axial_L3.8mm_D2.6mm_P7.50mm_Horizontal
C-speaker-front1: 0.1u; C_Axial_L3.8mm_D2.6mm_P7.50mm_Horizontal
C-speaker-receiver1: 0.1u; C_Axial_L3.8mm_D2.6mm_P7.50mm_Horizontal
J1: coin; PinHeader_2x05_P2.54mm_Vertical
J2: keypad; PinHeader_2x10_P2.54mm_Vertical
J3: display; PinHeader_2x13_P2.54mm_Vertical
J5: 4p4c; PinHeader_1x04_P2.54mm_Vertical
J6: card_reader; PinHeader_2x07_P2.54mm_Vertical
J7: motor; PinHeader_1x02_P2.54mm_Vertical
J8: power; PinHeader_1x02_P2.54mm_Vertical
R1, R2, R3, R4, R5, R7: 10k; R_Axial_DIN0204_L3.6mm_D1.6mm_P7.62mm_Horizontal
R6: 1k; R_Axial_DIN0204_L3.6mm_D1.6mm_P7.62mm_Horizontal
R8, R9: 10; R_Axial_DIN0204_L3.6mm_D1.6mm_P7.62mm_Horizontal
U1, U2: LM358; DIL08
speaker_front1: speaker_front; PinHeader_1x02_P2.54mm_Vertical

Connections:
2.5v: R3.2, R4.1, U1.3 (+)
5v: A1.5V, A1.VIN, A2.5V, A2.VIN, A3.2 (5V[1]), A3.4 (5V[2]), C-arduino1.1, C-arduino-display1.1, C-card1.2, C-coin1.1, C-opamp1.1, C-opamp2.1, C-power1.1, C-raspi1.1, J1.9, J3.2, J6.11, J8.1, R1.1, R2.1, R3.1, R5.2, U1.8 (V+), U2.8 (V+)
unnamed: C1.2, R6.2
unnamed: C2.1, R7.2, U1.1
unnamed: R6.1, R7.1, U1.2 (-)
unnamed: C3.1, R8.2, U1.5 (+)
unnamed: C4.1, U1.6 (-), U1.7
unnamed: C5.1, R9.2, U2.3 (+)
unnamed: C6.1, U2.1, U2.2 (-)
card_seated: J6.12
coin_1: A2.A3, J1.2
coin_2: J1.10
coin_3: J1.6
coin_sig: A2.A2, J1.3
disp_d0: A2.D5, J3.15
disp_d1: A2.D6, J3.13
disp_d2: A2.D7 (D7_INT4), J3.11
disp_d3: A2.D8, J3.9
disp_d4: A2.D9, J3.7
disp_d5: A2.D10, J3.5
disp_d6: A2.D11, J3.3
disp_d7: A2.D12, J3.1
disp_x1: A2.D4, J3.17
disp_x2: A2.A1, J3.19
disp_x3: A2.A0, J3.21
disp_x4: A2.D0 (D0/RX), J3.23
disp_x5: A2.D1 (D1/TX), J3.25
disp_x6: A2.D13, J3.20
gnd: A1.GND1 (GND), A1.GND2 (GND), A2.GND1 (GND), A2.GND2 (GND), A3.6 (GND[8]), A3.9 (GND[1]), A3.14 (GND[4]), A3.20 (GND[5]), A3.25 (GND[2]), A3.30 (GND[6]), A3.34 (GND[7]), A3.39 (GND[3]), C3.2, C5.2, C-arduino1.2, C-arduino-display1.2, C-card1.1, C-coin1.2, C-mic1.2, C-opamp1.2, C-opamp2.2, C-power1.2, C-raspi1.2, C-speaker-front1.2, C-speaker-receiver1.2, J1.1, J1.4, J1.5, J1.7, J1.8, J3.26, J5.3, J5.4, J6.2, J8.2, R4.2, U1.4 (V-), U2.4 (V-), speaker_front1.2
key_col1: A1.D4, J2.1
key_col2: A1.D9, J2.2
key_col3: A1.A0, J2.3
key_col4: A1.A1, J2.4
key_col5: A1.D11, J2.5
key_col6: A1.D5, J2.7
key_col7: A1.D7 (D7_INT4), J2.8
key_hook_common: J2.12
key_hook_down: J2.14
key_hook_up: J2.10
key_row1: A1.A4, J2.6
key_row2: A1.D8, J2.9
key_row3: A1.D10, J2.11
key_row4: A1.D12, J2.13
mag_cls: A1.A2, J6.9
mag_rcl: A1.D1 (D1/TX), J6.6
mag_rdt: A1.D0 (D0/RX), J6.4
mic+: C1.1, C-mic1.1, J5.1, R5.1
mic_amp: A1.A3, C2.2
miso: A1.MISO (SPI_MISO), A3.21 (GPIO9/MISO)
mosi: A1.MOSI (SPI_MOSI), A3.19 (GPIO10/MOSI)
motor+: A2.A5, J7.1
motor-: A2.A4, J7.2
pwm_speaker_front: A1.D6, R9.1
pwm_speaker_receiver: A1.D13, R8.1
sck: A1.SCK (SPI_SCK), A3.23 (GPIO11/SCLK)
scl: A1.D3 (D3/SCL), A2.D3 (D3/SCL), R2.2
sda: A1.D2 (D2/SDA), A2.D2 (D2/SDA), R1.2
speaker_front+: C6.2, C-speaker-front1.1, speaker_front1.1
speaker_receiver+: C4.2, C-speaker-receiver1.1, J5.2
ss: A1.SS (SPI_CS), A3.37 (GPIO26)

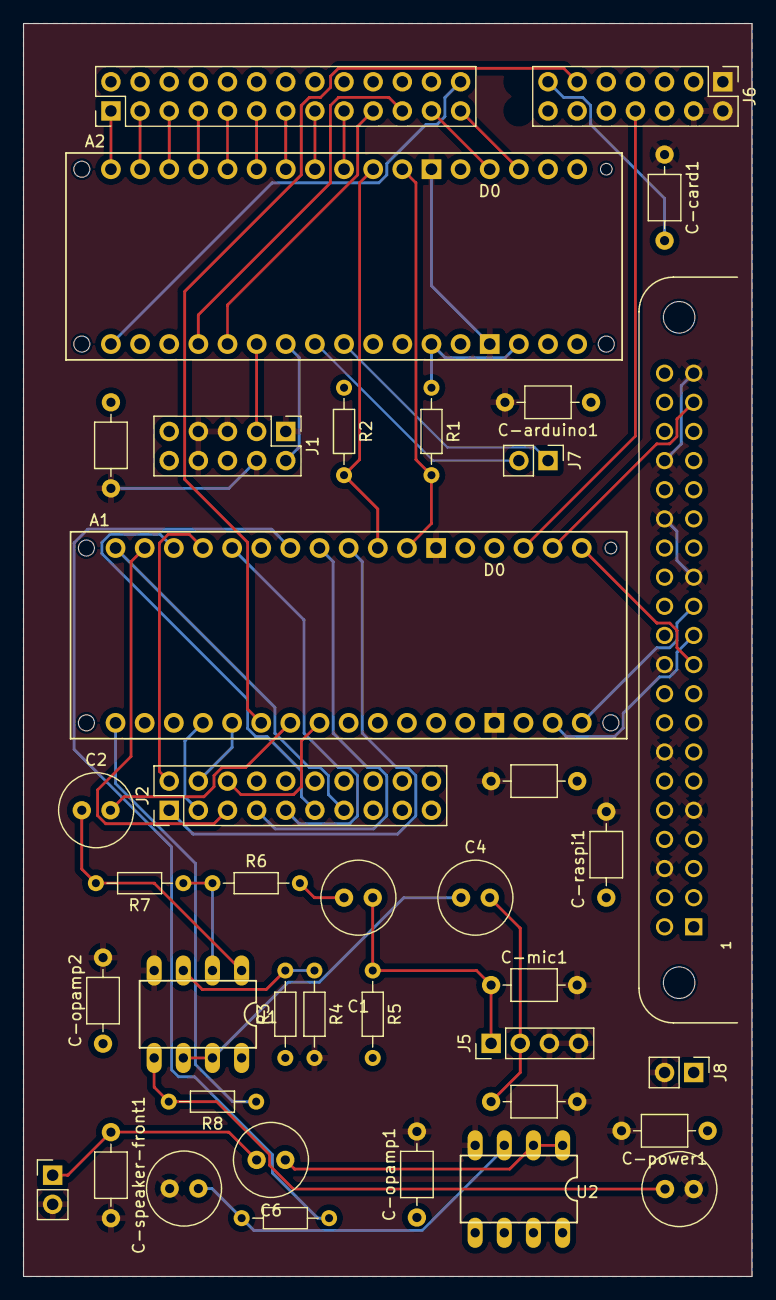
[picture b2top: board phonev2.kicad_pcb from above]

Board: 2 copper layers, 63.5 x 109.2 mm, 39 parts (0 on the bottom side), 54 nets.

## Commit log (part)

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2026-02-23 schematic updates
2026-02-26 pcb: phonev4 KiCad design with project footprint libraries
    - Add project-local footprint libs: ADA3708, audio, PCM_arduino-library, misc_footprints
    - Q1 THT: TO-220-3_Vertical_GSD for IRF9540N
    - R4, R5: 1k for Pi→Arduino reset (unconnected in schematic)
    - Updated fp-lib-table, BOM, README, audit script
    Made-with: Cursor
2026-02-26 pcb: BOM designator alignment and regenerated Gerbers
    - BOM: use schematic refs (C1-C12) instead of functional names
    - Gerbers: regenerate from phonev4.kicad_pcb
    - Add In1_Cu, In2_Cu for 4-layer board
    - Update PTH/NPTH drill files, job file
    Made-with: Cursor
2026-02-26 pcb: rename phonev4 to phonev5
    - Rename all KiCad project files (schematic, PCB, pro, prl, csv, rules)
    - Rename Gerbers and drill files to phonev5-*
    - Update project refs in kicad_sch, kicad_pcb, kicad_pro, gbrjob
    - Update Makefile, audit_schematic.py, README, AUDIT, DESIGN_OPTIONS
    - Update HARDWARE.md and root README
    Made-with: Cursor
2026-02-26 pcb: Gerber export cleanup - RS-274X, export script for JLCPCB zip
    - Disable Gerber X2 attributes (usegerberattributes no) to avoid JLCPCB
    preview parser issues
    - Add export_jlcpcb.sh: Gerbers + drills -> phonev5-gerbers.zip
    - BOM/CPL handled by KiCad JLCPCB plugin
    Made-with: Cursor
2026-02-26 pcb: clean up unused files, add JLCPCB workflow
    - Remove obsolete BOM/CPL CSVs and Python scripts (plugin handles these)
    - Remove redundant loose Gerber files (kept in zip only)
    - Remove outdated gerbers/ docs (BOM_VERIFICATION, CPL_ROOT_CAUSE, etc.)
    - Add JLCPCB_WORKFLOW.md: export script + plugin for BOM/CPL
    - Update .gitignore for PCB build artifacts (gerbers, jlcpcb, backups)
    - Update README Manufacturing section
2026-02-26 pcb: add gerbers/README.md for export output
    Made-with: Cursor
2026-02-26 pcb: single Gerber output to jlcpcb/production_files only
    - Export script outputs GERBER-phonev5.zip directly to jlcpcb/production_files/
    - Remove gerbers/ folder (was redundant)
    Made-with: Cursor
2026-02-26 pcb: clean old gerber files and zip before export
    Made-with: Cursor
2026-02-27 pcb: checkpoint before THT→SMD migration
    - 100nF caps: C_Disc_D5.0mm_W2.5mm_P2.50mm, LCSC C600221
    - Preserve current state before replacing THT with SMD
    Made-with: Cursor
2026-03-15 updated pcb
2026-06-11 config: strict range-checked validation with descriptive diagnostics
    config_validate() previously checked only call.cost_cents and
    system.update_interval_ms, and returned a bare pass/fail. A typo or an
    out-of-range value (e.g. web_server.port=99999, logging.level=INF,
    call.timeout_seconds=-1) sailed through, so the daemon would either
    start misconfigured or abort with only "Configuration validation
    failed" and no clue which setting was wrong.
